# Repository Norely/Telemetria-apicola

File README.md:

# Telemetria-apicola

# Integrantes:
 - Juan Sebastian Martinez Valbuena
 - Elkin Alejandro Romero Hernandez
 - Gustavo Olarte Romero
 - Norely Jimenez Melenge

# ¿En que consiste el producto?
El producto consiste es un sistema de embebido que permite sensar la temperatura y mantenerla desde los 12°C hasta los 35°C,ya que en un apiario es importante que la temperatura no exceda los 38°C,para evitar que las abejas realizan trabajo extra,como salir a traer agua o realizar ventilación con sus alas. Además cuenta con un sistema de GPs que envía una notificación al celular,  en el cual es necesario para obtener la certificación que identifique su posición geográfica.

El módulo medirá temperatura, humedad y llenado de los tanques. Los actuadores constaría de un ventilador para refrigerar el ambiente y una resistencia en caso de requerir aumento de temperatura. Cuando los tanques estén llenos el módulo envía un mensaje de alerta a la interfaz que se haya elegido. También se puede incluir un módulo de alimentación artificial para que suministre agua azucarada en caso de ser necesario (se realizará 45 días antes de la floración y se suspende al inicio de la misma). 

# Componentes basicos
- ESP32 (Microcontrolador)
- Raspberry (Servidores)
- Sensor de humedad DHT11 (DIGITAL)  (12 - 35)°C
- Pantalla OLED
- Ventilador
- Microbomba
- Neo m7 (GPS)
- Regulador ASM1117 3.3V
- Driver L293D
- Convertidor MT3608
- BQ24070

# Requerimientos funcionales
* El apiario debe recopilar constantemente las variables de interés (temperatura y humedad)
* El sistema recolecta datos automáticamente para enviarlos a un servidor local.
* Mantener un ambiente controlado (parámetros ambientales)
* El sistema tendrá una Interfaz hombre máquina que permita la visualización de los parámetros medidos
* El apiario debe poseer módulos removibles para la obtención de miel.
* El sistema cuenta con monitoreo y control por parte del usuario en caso de falla de cualquier dispositivo electrónico.

# Requerimientos no funcionales
* El apiario debe funcionar todo el día.
* Debe garantizar la calidad apropiada de la miel
* El apiario debe usarse sólo por personal calificado.
* La interfaz hombre-máquina debe ser responsive.

# Hardware
***ESP 32***

Para pruebas del firmware y algunos componentes se hará uso de la siguiente tarjeta:

|Pin| Protocolo | Nombre |Dispositivo|
|-----|------|------|-----|
|33|I2C|SDA|Pantalla|
|36|I2C|SCL|Pantalla|
|34|UART|Rx|USB|
|35|UART|Tx|USB|
|23|UART|Rx|GPS|
|27|UART|Tx|GPS|
|24|GPIO| |Sensor T/H|
|26| | |Ventilador|
|29| | |Microbomba|
|13| | |Rele Bombilla|

Este tiene las siguientes caracteristicas:
- Procesador Tensilica Xtensa 32bits LX6 hasta 240MHz.
- Wi-Fi: 802.11b/g/n/e/i (802.11n @ 2.4 Ghz hasta 150 Mbit/s).
- Bluetooth: v4.2 BR/EDR y bluetooth  Low Energy (BLE).
- Rom:448 KiB.
- SRAM: 520 KiB.
- RTC slow SRAM: 8 KiB.
- RTC fast SRAM: 8 KiB.
- eFuse: 1 Kbit.
- Flash embebida: 0 MiB (ESP32-D0WDQ6, ESP32-D0WD, and ESP32-S0WD chips); 2 MiB (ESP32-D2WD chip); 4 MiB (ESP32-PICO-D4 SIP module).
- Periféricos compatibles: ADC, DAC, I2C, UART, Interfaz CAN 2.0, SPI, I2S, RMII y PWM entre otros.
- Seguridad tipo IEEE 802.11, WFA, WPA/WPA2 y WAPI.
- Encriptación de memoria Flash.
- Criptografía soportada por acelerador de hardware: AES, SHA-2, RSA, ECC, RNG.
- Voltaje de trabajo 3.3VDC.
- Energía y datos  via conector microUSB 5VDC.

En la tarjeta que estamos desarrollando se emplea el siguiente módulo (Esp 32-WROOM-32D): 

Este se encuentra en SIGMA ELECTRONICA ([ESP 32](https://www.sigmaelectronica.net/producto/esp32-wroom-32d/)) y tambien su [Hoja de datos](https://github.com/Norely/Telemetria-apicola/blob/main/Hojas%20de%20datos/ESP32-WROOM-32D_pdf.pdf) de donde se puede obtener el esquematico de los perifericos para el módulo:

***Raspberry PI4-4GB***

Esta tarjeta se considera para el montaje del servidor en donde se planea guardar la información obtenida del proyecto. 

Especificaciones:
- BCM2711 Broadcom, Quad Core Cortex-A72.
- 64-bit SoC @ 1,5 GHz.
- Memoria RAM: 4 GB.
- 2.4 GHz y 5.0 GHz IEEE 802.11b/g/n/ac inalámbrico LAN.
- Bluetooth 5.0 BLE.
- Gigabit Ethernet.
- 2 Puertos USB 2.0.
- 2 Puertos USB 3.0.
- Conector GPIO estándar de 40 pines (Totalmente compatible con las placas de desarrollo Raspberry PI anteriores).
- 2 puertos micro HDMI (compatible con hasta 4Kp60).
- Puerto de visualización MIPI DSI de 2 vías.
- Puerto de camara MIPI de 2 carriles.
- Puerto de vídeo compuesto y audio estéreo de 4 polos.
- H.265 (decodificador de 4Kp60).
- H.264 (decodificador 1080p60, 1080p30).
- OpenGL ES 3.0 gráficos.
- Ranura para tarjeta Micro SD para cargar el sistema operativo y el almacenamiento de datos.
- Alimentación de entrada por conector USB Tipo C: 5V – 3A.
- Alimentación de entrada por conector GPIO: 5V – 3A.
- Alimentación sobre Ethernet (PoE) habilitada (requiere un complemento adicional PoE por separado): 5V – 3A.

Este se encuentra en SIGMA ELECTRONICA ([RPI4-4GB](https://www.sigmaelectronica.net/producto/rpi4-4gb/)) y tambien su [Hoja de datos](https://github.com/Norely/Telemetria-apicola/blob/main/Hojas%20de%20datos/RASP.pdf)

***Sensor de humedad DHT11***

Este sensor permite obtener la lectura de temperatura y humedad, ademas su señal es digital por lo que facilita su comunicacion con la ESP 32.

Especificaciones:
- humedad relativa 
-Resolución: 16 bit 
- Repetibilidad: ± 1% HR 
- Precisión: En 25 ℃ ± 5% de humedad relativa 
- Intercambiabilidad: totalmente intercambiables 
- Tiempo de respuesta: 1 / e (63%) de 25 ℃ 6s 1m / s 6s aire 
- Histéresis: <± 0,3% HR 
- Estabilidad a largo plazo: <± 0.5% RH / yr in temperatura 
- Resolución: 16 bit 
- Repetibilidad: ± 0,2 ℃ 
- Rango: A los 25 ℃ ± 2 ℃ 
- Tiempo de respuesta: 1 / e (63%) 10S 
- Características eléctricas 
- Fuente de alimentación: CC 3.5 ~ 5.5V 
- Corriente de alimentación: medida 0.3mA espera 60μ A 
- Periodo de muestreo: más de 2 segundos

Este se encuentra en SIGMA ELECTRONICA ([DHT11](https://www.sigmaelectronica.net/producto/dht11/)) y tambien su [Hoja de datos](https://github.com/Norely/Telemetria-apicola/blob/main/Hojas%20de%20datos/DHT11.pdf).

***Pantalla OLED***

Se elige una pantalla OLED como recomendación del docente porque es mas eficiente energeticamente y ademas a la cantidad de pixeles que manejan.

Especificaciones:
- No necesita backlight.
- Color:Azul
- Resolución: 128x64.
- Voltaje: 3 a 5V.
- Temperatura de trabajo: -30ºC a 70ºC.
- Tamaño: 27 x 27 x 4.1 mm
- Interfaz: I2C IIC TWI
- Driver: SSD1306
- Consumo: 0.08W

Este se encuentra en Dualtronica ([Pantalla OLED](https://dualtronica.com/pantallas/396-pantalla-oled-096-azul-comunicacion-i2c.html)). La [Hoja de datos](https://github.com/Norely/Telemetria-apicola/blob/main/Hojas%20de%20datos/SSD1306.pdf) corresponde al driver SSD1306 .

***Ventilador***

El medio de refrigeracion que se empleará será un ventilador PI.

Especificaciones: 
- Voltaje de funcionamiento: 5 V.
- Corriente nominal: 0.2 A.
- Dimensiones: 30 mm x 30 mm x 10 mm.

Este se encuentra en SIGMA ELECTRONICA ([Ventilador RPI](https://www.sigmaelectronica.net/producto/ventilador-pi/)) y su [Hoja de datos](https://github.com/Norely/Telemetria-apicola/blob/main/Hojas%20de%20datos/VENTILADOR.pdf).

***Microbomba***

Para surtir alimentación artificial al apiario, se emplea el uso de esta microbomba. Se eligío por encima de la valvula solenoide porque esta requiere un caudal minimo ademas de su relativo costo elevado. 

Especificaciones:
- Voltaje de Alimentación: 2.5-6VDC.
- Elevación máxima: 40-110cm.
- Caudal: 80-100L/H.
- Diámetro exterior de la salida de agua: 7.5 mm.
- Diámetro interior de salida de agua: 4.7 mm.
- Diámetro : Aprox. 24 mm.
- Longitud: Aprox. 45 mm.
- Altura: aprox. 33 mm.
- Material: Plástico.
- Vida útil de trabajo continuo de 500 horas.

Este se encuentra en SIGMA ELECTRONICA ([Microbomba](https://www.sigmaelectronica.net/producto/sig0833/)).

***Neo M6***

Se emplea el módulo NEO-6M para emplearlo a parte de la tarjeta a desarrollar dadas las condiciones que requiere un modulo gps en la misma tarjeta como estar lejos de ciertos componentes como capacitores, ademas de la antena de la esp 32 con la que podria haber interferencia.

Especificaciones:
- Ultra sensibilidad: -165dBm
- 22 tracking/66 acquisition-channel receiver
- Coporta estándares WAAS/EGNOS/MSAS/GAGAN
- Frecuencia de actualización 5Hz velocidad de desplazamiento máxima: 500m/seg
- Protocolo NMEA  (a 9600bps)
- 01 puerto serial
- Antena incorporada de 18.2 x 18.2 x 4.0 mm
- Rango de temperatura: -40 to 85 C
- Cumple estándar RoHS
- Tamano reducido 30mm x20mm x 11.4mm

Este se encuentra en Dualtronica ([GPS NEO-6M](https://dualtronica.com/modulos/86-modulo-gps-neo-6m.html)) y su [Hoja de datos](https://github.com/Norely/Telemetria-apicola/blob/main/Hojas%20de%20datos/GY-NEO-6M-V2-pdf.pdf).

# Software

Para esta parte se realiza la [instalación](https://docs.micropython.org/en/latest/esp32/tutorial/intro.html#esp32-intro) para el ESP-32, del firmware mycropython. 
  
Este compilador permite realizar algunas acciones como la manipulación de los pines del microcontrolador, Interactuar con los protocolos de comunicacion (I2C, SPI, PWM, etc), Manejo de tiempos entre muchas otras.

## Ejemplos:

#### Pins
~~~
from machine import Pin

p0 = Pin(0, Pin.OUT)    # create output pin on GPIO0
p0.on()                 # set pin to "on" (high) level
p0.off()                # set pin to "off" (low) level
p0.value(1)             # set pin to on/high

p2 = Pin(2, Pin.IN)     # create input pin on GPIO2
print(p2.value())       # get value, 0 or 1

p4 = Pin(4, Pin.IN, Pin.PULL_UP) # enable internal pull-up resistor
p5 = Pin(5, Pin.OUT, value=1) # set pin high on creation
~~~

#### Protocolo
~~~
from machine import Pin, SoftI2C

i2c = SoftI2C(scl=Pin(5), sda=Pin(4), freq=100000)

i2c.scan()              # scan for devices

i2c.readfrom(0x3a, 4)   # read 4 bytes from device with address 0x3a
i2c.writeto(0x3a, '12') # write '12' to device with address 0x3a

buf = bytearray(10)     # create a buffer with 10 bytes
i2c.writeto(0x3a, buf)  # write the given buffer to the peripheral
~~~

#### Tiempo
~~~
import time

time.sleep(1)           # sleep for 1 second
time.sleep_ms(500)      # sleep for 500 milliseconds
time.sleep_us(10)       # sleep for 10 microseconds
start = time.ticks_ms() # get millisecond counter
delta = time.ticks_diff(time.ticks_ms(), start) # compute time difference
~~~

# Modelo 3D Diseño PCB

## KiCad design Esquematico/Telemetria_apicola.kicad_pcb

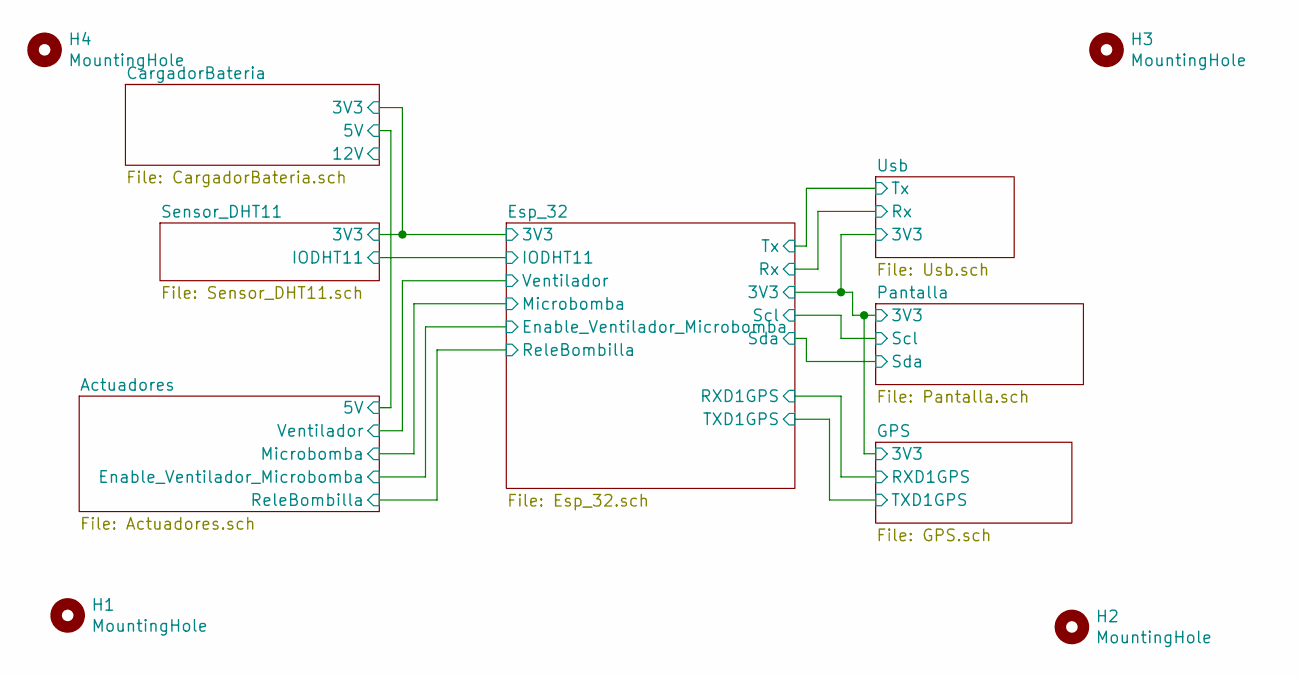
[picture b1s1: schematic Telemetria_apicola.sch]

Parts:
H1, H2, H3, H4: MountingHole; MountingHole_3.2mm_M3_ISO7380

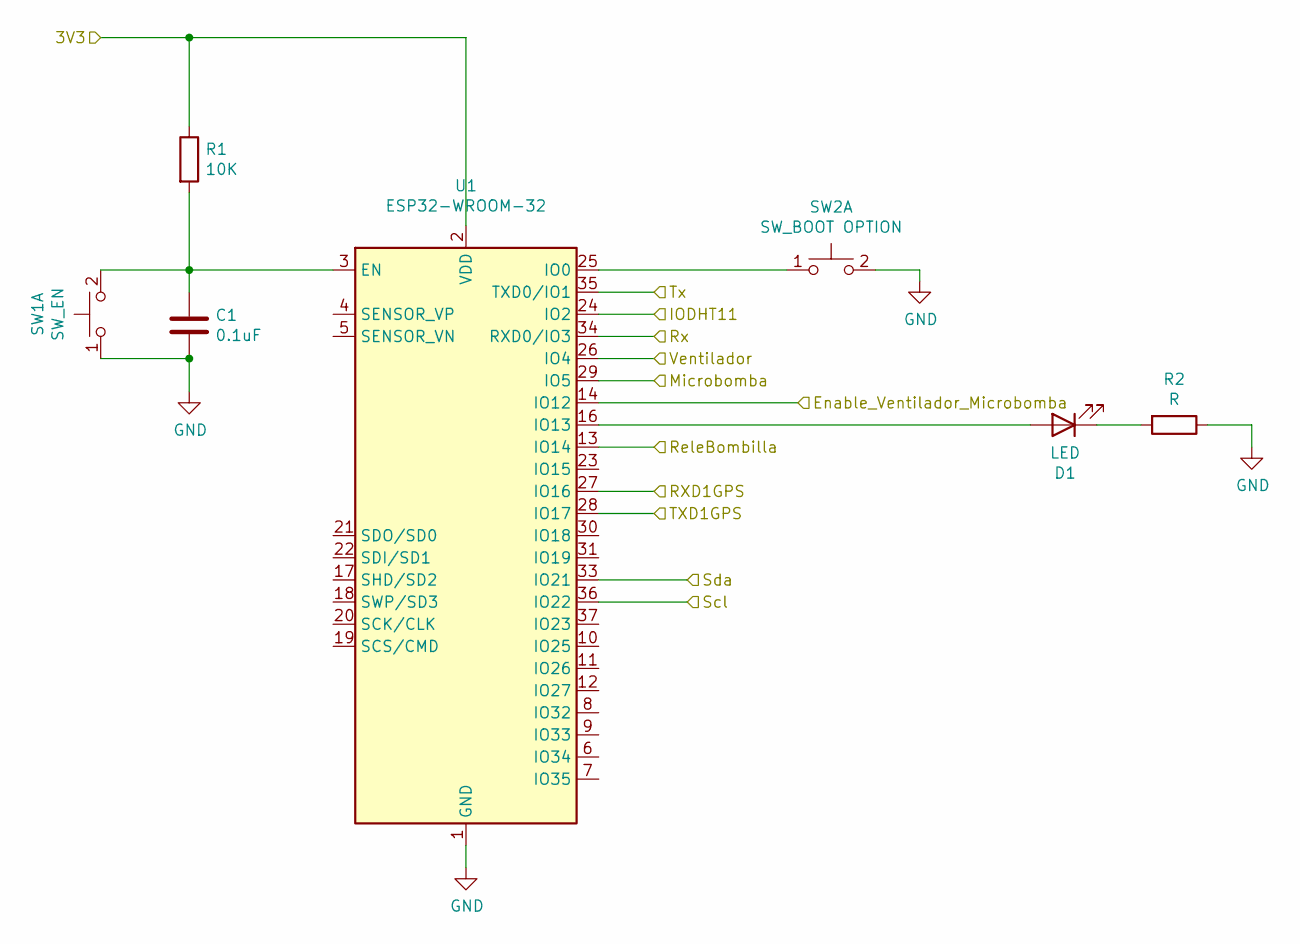
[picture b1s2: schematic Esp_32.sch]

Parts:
C1: 0.1uF; C_0805_2012Metric_Pad1.18x1.45mm_HandSolder
D1: LED; LED_D3.0mm
R1: 10K; R_0805_2012Metric_Pad1.20x1.40mm_HandSolder
R2: R; R_0805_2012Metric_Pad1.20x1.40mm_HandSolder
SW1: SW_EN; SW_Push_1P1T_NO_CK_KMR2
SW2: SW_BOOT OPTION; SW_Push_1P1T_NO_CK_KMR2
U1: ESP32-WROOM-32

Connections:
/Actuadores/Enable_Ventilador_Microbomba: U1.14 (IO12); also elsewhere on the board
/Actuadores/Microbomba: U1.29 (IO5); also elsewhere on the board
/Actuadores/ReleBombilla: U1.13 (IO14); also elsewhere on the board
/Actuadores/Ventilador: U1.26 (IO4); also elsewhere on the board
/CargadorBateria/3V3: R1.1, U1.2 (VDD); also elsewhere on the board
/Esp_32/IODHT11: U1.24 (IO2); also elsewhere on the board
/Esp_32/RXD1GPS: U1.27 (IO16); also elsewhere on the board
/Esp_32/Rx: U1.34 (RXD0/IO3); also elsewhere on the board
/Esp_32/Scl: U1.36 (IO22); also elsewhere on the board
/Esp_32/Sda: U1.33 (IO21); also elsewhere on the board
/Esp_32/TXD1GPS: U1.28 (IO17); also elsewhere on the board
/Esp_32/Tx: U1.35 (TXD0/IO1); also elsewhere on the board
GND: C1.2, R2.1, SW1.1 (C), SW2.2 (D), U1.1 (GND), U1.15 (GND), U1.38 (GND), U1.39 (GND); also elsewhere on the board
unnamed: C1.1, R1.2, SW1.2 (D), U1.3 (EN)
unnamed: D1.1 (K), R2.2
unnamed: D1.2 (A), U1.16 (IO13)
unnamed: SW2.1 (C), U1.25 (IO0)

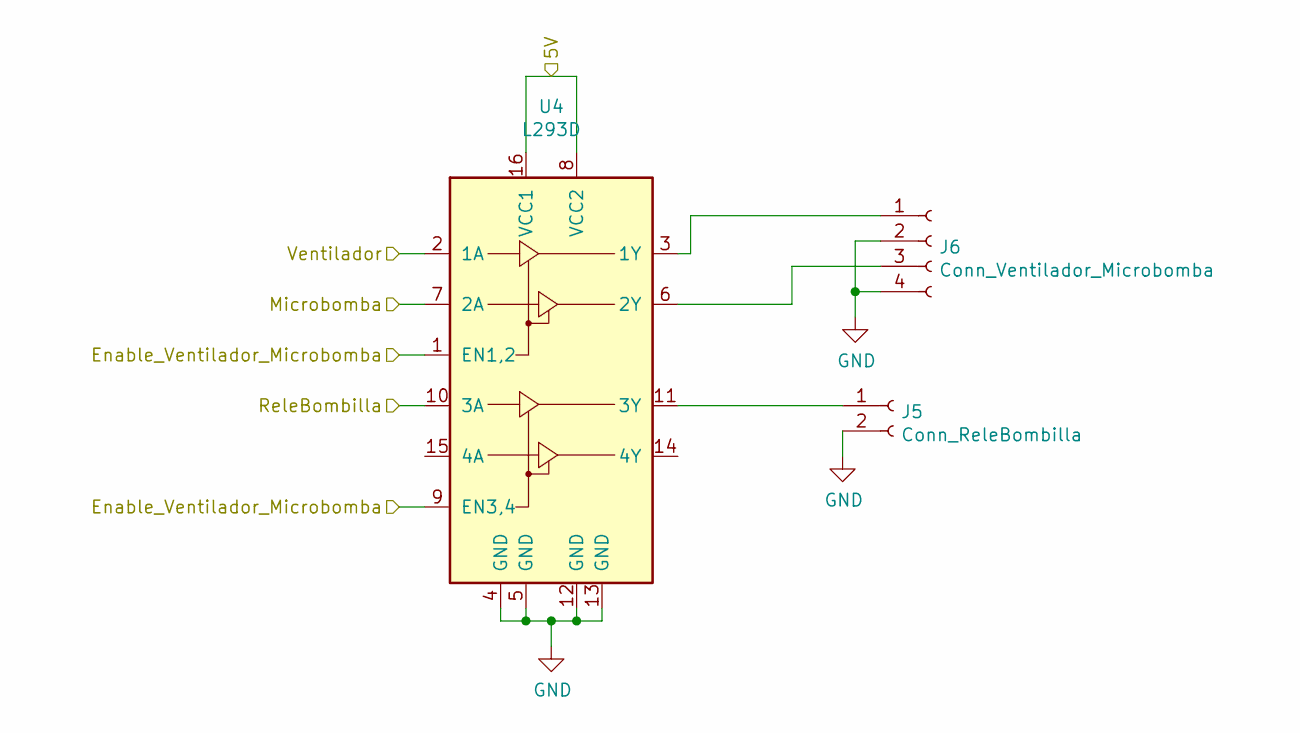
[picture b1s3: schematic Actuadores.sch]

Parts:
J5: Conn_ReleBombilla
J6: Conn_Ventilador_Microbomba
U4: L293D; DIP-16_W7.62mm

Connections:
/Actuadores/5V: U4.8 (VCC2), U4.16 (VCC1); also elsewhere on the board
/Actuadores/Enable_Ventilador_Microbomba: U4.1 (EN1,2), U4.9 (EN3,4); also elsewhere on the board
/Actuadores/Microbomba: U4.7 (2A); also elsewhere on the board
/Actuadores/ReleBombilla: U4.10 (3A); also elsewhere on the board
/Actuadores/Ventilador: U4.2 (1A); also elsewhere on the board
GND: J5.2, J6.2, J6.4, U4.4 (GND), U4.5 (GND), U4.12 (GND), U4.13 (GND); also elsewhere on the board
unnamed: J5.1, U4.11 (3Y)
unnamed: J6.1, U4.3 (1Y)
unnamed: J6.3, U4.6 (2Y)

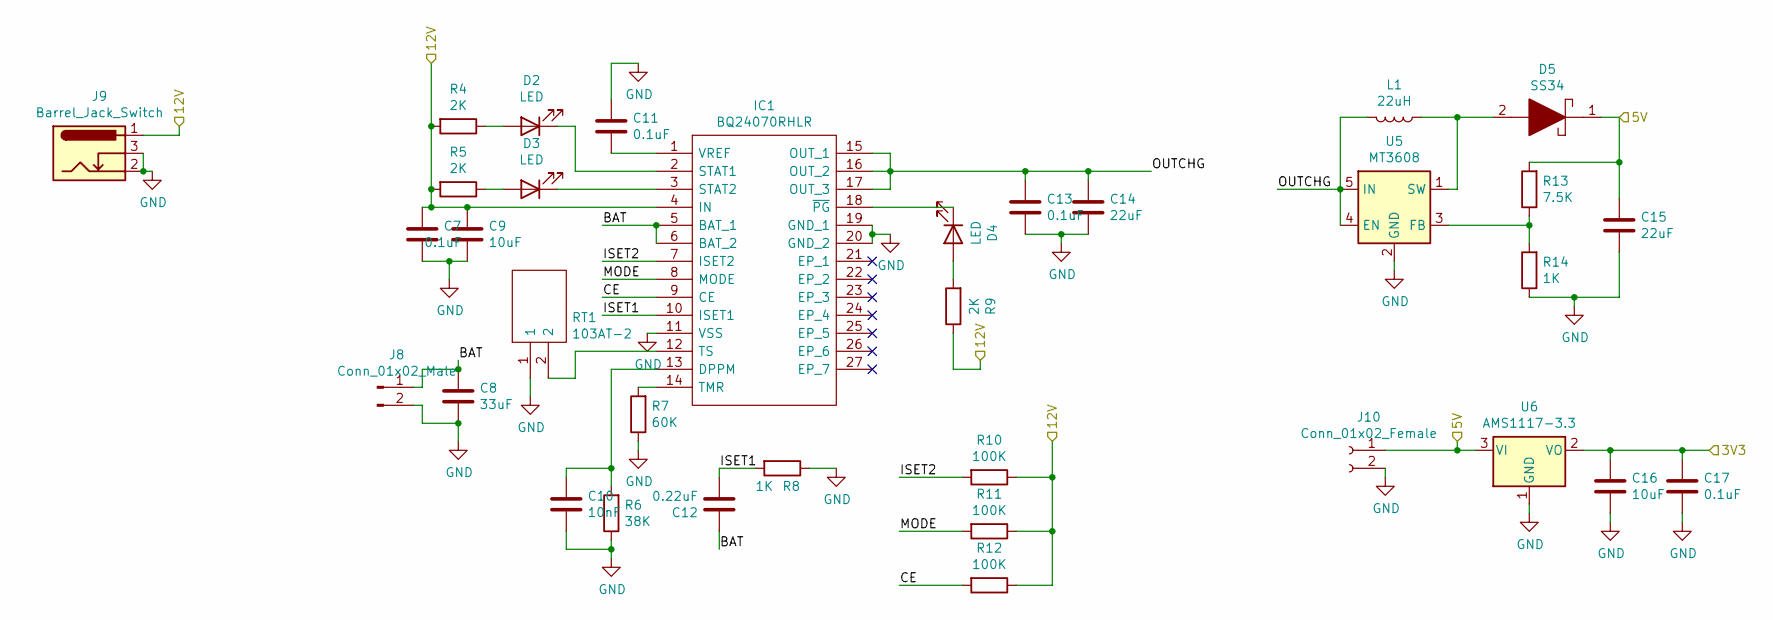
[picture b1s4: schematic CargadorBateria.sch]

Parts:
C7, C11, C13, C17: 0.1uF; C_0805_2012Metric_Pad1.18x1.45mm_HandSolder
C8: 33uF; C_0805_2012Metric_Pad1.18x1.45mm_HandSolder
C9, C16: 10uF; C_0805_2012Metric_Pad1.18x1.45mm_HandSolder
C10: 10nF; C_0805_2012Metric_Pad1.18x1.45mm_HandSolder
C12: 0.22uF; C_0805_2012Metric_Pad1.18x1.45mm_HandSolder
C14, C15: 22uF; C_0805_2012Metric_Pad1.18x1.45mm_HandSolder
D2, D3, D4: LED; LED_0805_2012Metric_Pad1.15x1.40mm_HandSolder
D5: SS34; DIONM7959X262N; Manufacturer_Part_Number SS34
IC1: BQ24070RHLR; BQ24032ARHLR; Manufacturer_Part_Number BQ24070RHLR; Mouser Part Number 595-BQ24070RHLR
J8: Conn_01x02_Male; PinHeader_1x02_P2.54mm_Vertical
J9: Barrel_Jack_Switch; BarrelJack_CUI_PJ-102AH_Horizontal
J10: Conn_01x02_Female; PinSocket_1x02_P2.54mm_Vertical
L1: 22uH; L_0805_2012Metric
R4, R5, R9: 2K; R_0805_2012Metric_Pad1.20x1.40mm_HandSolder
R6: 38K; R_0805_2012Metric_Pad1.20x1.40mm_HandSolder
R7: 60K; R_0805_2012Metric_Pad1.20x1.40mm_HandSolder
R8, R14: 1K; R_0805_2012Metric_Pad1.20x1.40mm_HandSolder
R10, R11, R12: 100K; R_0805_2012Metric_Pad1.20x1.40mm_HandSolder
R13: 7.5K; R_0805_2012Metric_Pad1.20x1.40mm_HandSolder
RT1: 103AT-2; 103AT2; Manufacturer_Part_Number 103AT-2; Mouser Part Number 954-103AT-2
U5: MT3608; SOT-23-6
U6: AMS1117-3.3; SOT-223-3_TabPin2

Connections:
/Actuadores/5V: C15.1, D5.1, J10.1, R13.2, U6.3 (VI); also elsewhere on the board
/CargadorBateria/3V3: C16.1, C17.1, U6.2 (VO); also elsewhere on the board
/CargadorBateria/12V: C7.1, C9.1, IC1.4 (IN), J9.1, R4.2, R5.2, R9.1, R10.1, R11.1, R12.1
/CargadorBateria/BAT: C8.1, C12.1, IC1.5 (BAT_1), IC1.6 (BAT_2), J8.1
/CargadorBateria/CE: IC1.9 (CE), R12.2
/CargadorBateria/ISET1: C12.2, IC1.10 (ISET1), R8.2
/CargadorBateria/ISET2: IC1.7 (ISET2), R10.2
/CargadorBateria/MODE: IC1.8 (MODE), R11.2
/CargadorBateria/OUTCHG: C13.1, C14.1, IC1.15 (OUT_1), IC1.16 (OUT_2), IC1.17 (OUT_3), L1.2, U5.4 (EN), U5.5 (IN)
GND: C7.2, C8.2, C9.2, C10.2, C11.1, C13.2, C14.2, C15.2, C16.2, C17.2, IC1.11 (VSS), IC1.19 (GND_1), IC1.20 (GND_2), J8.2, J9.2, J9.3, J10.2, R6.1, R7.1, R8.1, R14.1, RT1.1, U5.2 (GND), U6.1 (GND); also elsewhere on the board
unnamed: C10.1, IC1.13 (DPPM), R6.2
unnamed: C11.2, IC1.1 (VREF)
unnamed: D2.1 (K), IC1.2 (STAT1)
unnamed: D2.2 (A), R4.1
unnamed: D3.1 (K), IC1.3 (STAT2)
unnamed: D3.2 (A), R5.1
unnamed: D4.1 (K), IC1.18 (~PG)
unnamed: D4.2 (A), R9.2
unnamed: D5.2, L1.1, U5.1 (SW)
unnamed: IC1.12 (TS), RT1.2
unnamed: IC1.14 (TMR), R7.2
unnamed: R13.1, R14.2, U5.3 (FB)

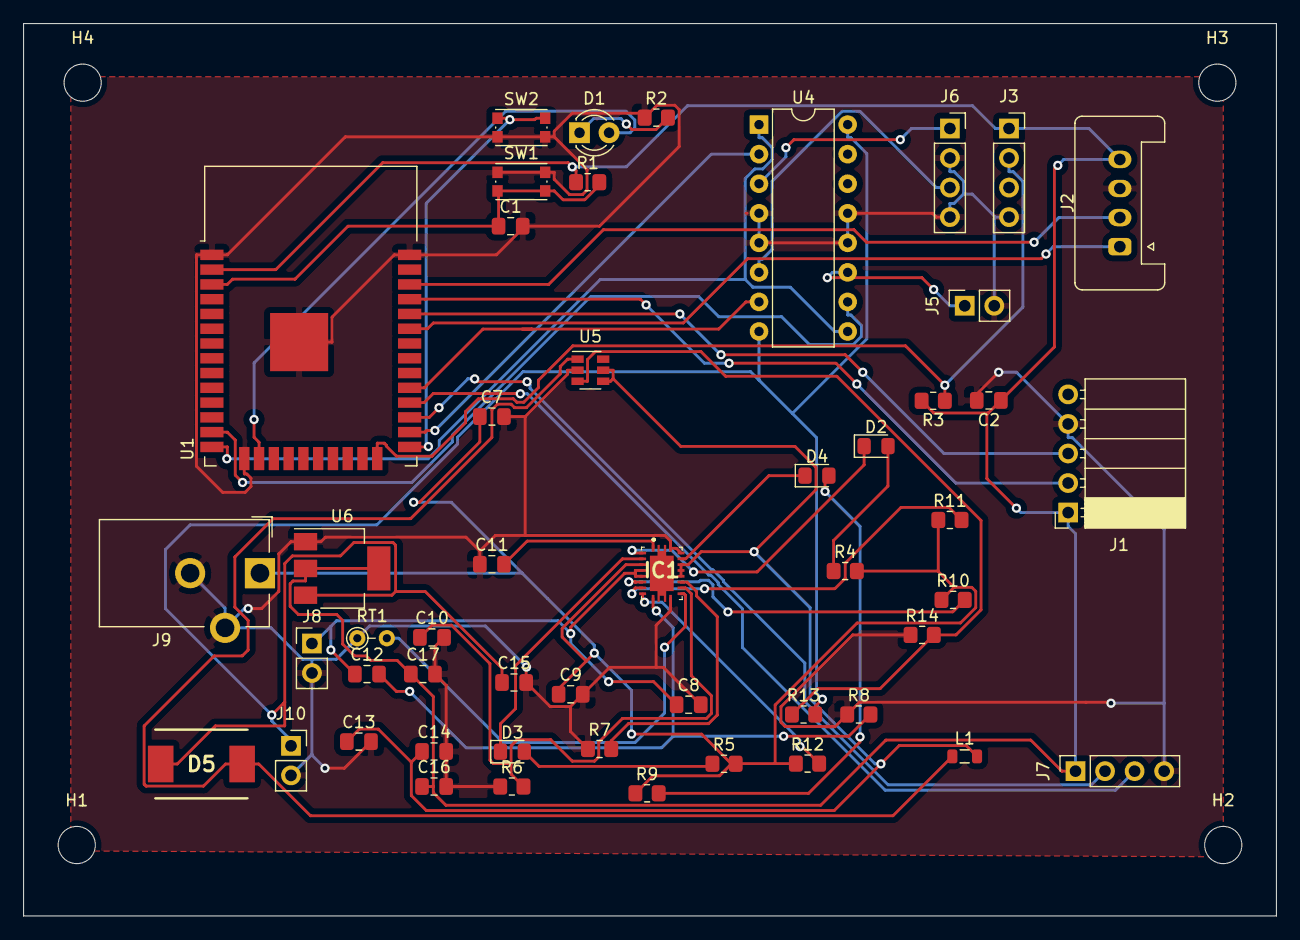
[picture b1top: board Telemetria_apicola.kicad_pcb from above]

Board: 2 copper layers, 107.7 x 76.7 mm, 54 parts (0 on the bottom side), 40 nets.

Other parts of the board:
C2: 100nF; C_0805_2012Metric_Pad1.18x1.45mm_HandSolder
J1: Conn_USB; PinSocket_1x05_P2.54mm_Horizontal
J2: Conn_PANTALLA; Stocko_MKS_1654-6-0-404_1x4_P2.50mm_Vertical
J3: Conn_DHT11; PinSocket_1x04_P2.54mm_Vertical
J7: Conn_GPS; PinSocket_1x04_P2.54mm_Vertical
R3: 5K; R_0805_2012Metric_Pad1.20x1.40mm_HandSolder

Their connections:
/CargadorBateria/3V3: C2.1, J1.1, J2.4, J3.1, J7.1, R3.2; also elsewhere on the board
/Esp_32/IODHT11: J3.2, R3.1; also elsewhere on the board
/Esp_32/RXD1GPS: J7.2; also elsewhere on the board
/Esp_32/Rx: J1.3; also elsewhere on the board
/Esp_32/Scl: J2.2; also elsewhere on the board
/Esp_32/Sda: J2.1; also elsewhere on the board
/Esp_32/TXD1GPS: J7.3; also elsewhere on the board
/Esp_32/Tx: J1.2; also elsewhere on the board
GND: C2.2, J1.4, J2.3, J3.4, J7.4; also elsewhere on the board

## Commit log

2021-11-02 Create Diagrama de bloques
2021-12-02 Esquematico
2021-12-02 Creación Esquematico
2021-12-14 Foot prints
2021-12-14 se trajeron los datos de los compañeros
2022-01-05 sistema de carga de bateria y tension de salida a 5v y 3v3
2022-01-13 cambios termistor
2022-01-16 Carga elementos PCB
2022-01-16 footprints terminados
2022-01-17 cambios adicionales
2022-01-17 Actualización Readme
2022-01-24 Actualización PCB
2022-01-25 Creacion carpeta software
2022-01-25 archivo nuevo de pantalla
2022-01-25 Modificacion PCB
2022-01-31 Actualización Software GPS, DHT
2022-02-01 Archivo pwm añadido a software
2022-02-09 Creación PDF esquematico
2022-02-10 docuementos adicionales
2022-02-10 Se sube documento de evidencias Raspberry Pi
2022-02-10 Se sube archivo de protocolo MQTT para probar servidor RPI4
